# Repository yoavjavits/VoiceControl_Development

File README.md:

# Voice Control

This repo shows our development process.

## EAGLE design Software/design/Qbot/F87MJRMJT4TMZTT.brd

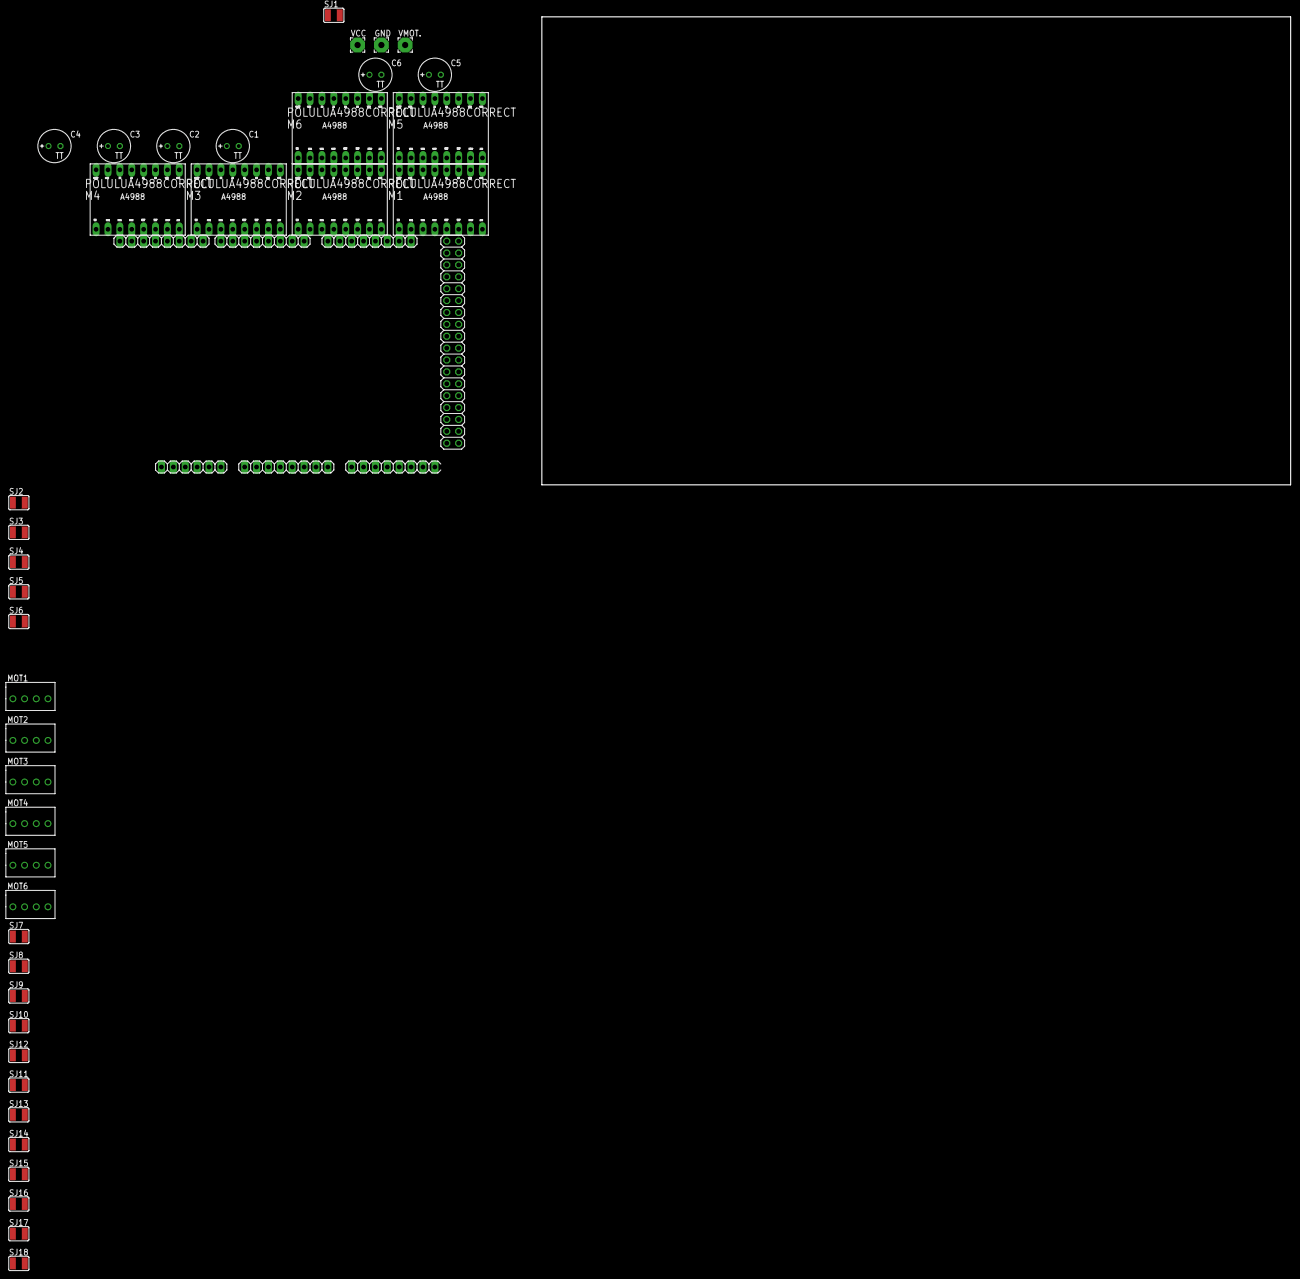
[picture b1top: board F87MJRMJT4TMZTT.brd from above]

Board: 2 copper layers, 160.0 x 100.0 mm, 40 parts (0 on the bottom side), 61 nets, no tracks yet.

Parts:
C1, C2, C3, C4, C5, C6: 100µF; TT2D7
GND: 3,17/1,3
IC2: MEGA_ARDUINO_1
M1, M2, M3, M4, M5, M6: POLULUA4988CORRECT; POLULU_A4988
MOT1, MOT2, MOT3, MOT4, MOT5, MOT6: 4PIN_JST
SJ1, SJ2, SJ3, SJ4, SJ5, SJ6, SJ7, SJ8, SJ9, SJ10, SJ11, SJ12, SJ13, SJ14, SJ15, SJ16, SJ17, SJ18: SJW
VCC: 3,17/1,3
VMOT.: 3,17/1,3

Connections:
+5V: IC2.3, IC2.47, IC2.48
GND: C1.-, C2.-, C3.-, C4.-, C5.-, C6.-, GND.1, IC2.4, IC2.5, IC2.45, IC2.81, IC2.82, M1.GND@1, M1.GND@2, M2.GND@1, M2.GND@2, M3.GND@1, M3.GND@2, M4.GND@1, M4.GND@2, M5.GND@1, M5.GND@2, M6.GND@1, M6.GND@2
MOT1DIR: IC2.33, M1.STEP
MOT1STEP: IC2.34, M1.DIR
MOT2DIR: IC2.35, M2.STEP
MOT2STEP: IC2.36, M2.DIR
MOT3DIR: IC2.37, M3.STEP
MOT3STEP: IC2.38, M3.DIR
MOT4DIR: IC2.39, M4.STEP
MOT4STEP: IC2.40, M4.DIR
MOT5DIR: IC2.41, M5.STEP
MOT5STEP: IC2.42, M5.DIR
MOT6DIR: IC2.43, M6.STEP
MOT6STEP: IC2.44, M6.DIR
unnamed: M1.MS1, SJ1.2
unnamed: M1.MS2, SJ2.2
unnamed: M1.MS3, SJ3.2
unnamed: M1.2B, MOT1.1
unnamed: M1.2A, MOT1.2
unnamed: M1.1A, MOT1.3
unnamed: M1.1B, MOT1.4
unnamed: M2.MS1, SJ4.2
unnamed: M2.MS2, SJ5.2
unnamed: M2.MS3, SJ6.2
unnamed: M2.2B, MOT2.1
unnamed: M2.2A, MOT2.2
unnamed: M2.1A, MOT2.3
unnamed: M2.1B, MOT2.4
unnamed: M2.!RESET, M2.!SLEEP
unnamed: M3.2B, MOT3.1
unnamed: M3.2A, MOT3.2
unnamed: M3.1A, MOT3.3
unnamed: M3.1B, MOT3.4
unnamed: M3.!RESET, M3.!SLEEP
unnamed: M4.2B, MOT4.1
unnamed: M4.2A, MOT4.2
unnamed: M4.1A, MOT4.3
unnamed: M4.1B, MOT4.4
unnamed: M4.!RESET, M4.!SLEEP
unnamed: M4.MS1, SJ10.2
unnamed: M4.MS2, SJ11.2
unnamed: M4.MS3, SJ12.2
unnamed: M5.2B, MOT5.1
unnamed: M5.2A, MOT5.2
unnamed: M5.1A, MOT5.3
unnamed: M5.1B, MOT5.4
unnamed: M5.!RESET, M5.!SLEEP
unnamed: M5.MS1, SJ13.2
unnamed: M5.MS2, SJ14.2
unnamed: M5.MS3, SJ15.2
unnamed: M6.2B, MOT6.1
unnamed: M6.2A, MOT6.2
unnamed: M6.1A, MOT6.3
unnamed: M6.1B, MOT6.4
unnamed: M6.!RESET, M6.!SLEEP
unnamed: M6.MS1, SJ16.2
unnamed: M6.MS2, SJ17.2
unnamed: M6.MS3, SJ18.2
unnamed: M1.!RESET, M1.!SLEEP
VCC: IC2.6, M1.VDD, M2.VDD, M3.VDD, M4.VDD, M5.VDD, M6.VDD, SJ1.1, SJ2.1, SJ3.1, SJ4.1, SJ5.1, SJ6.1, SJ7.1, SJ8.1, SJ9.1, SJ10.1, SJ11.1, SJ12.1, SJ13.1, SJ14.1, SJ15.1, SJ16.1, SJ17.1, SJ18.1, VCC.1
VMOT: C1.+, C2.+, C3.+, C4.+, C5.+, C6.+, M1.VMOT, M2.VMOT, M3.VMOT, M4.VMOT, M5.VMOT, M6.VMOT, VMOT..1

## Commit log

2022-03-30 Second Comment
2022-03-30 Second Commit
2022-03-30 Third Commit
2022-03-30 Hello
2022-04-05 Create voice recognition links
2022-04-05 I2S first try
2022-04-06 Create audio_serial_plotter
2022-04-06 Create recorder
2022-04-06 Create upload_to_browser
2022-04-06 Rename voice recognition links to voice_recognition_links.md
2022-04-12 Rename other_gits.md to Link To Other GitHub Projects
2022-04-12 Rename voice_recognition_links.md to Voice Recognition Links.md
2022-04-12 Rename Audio_Device.md to Audio Device.md
2022-04-12 Update Link To Other GitHub Projects
2022-04-12 WifiIntercom Upload
2022-04-12 Upload WifiIntercom
2022-04-13 Start Work Detector
2022-04-13 Rename Link To Other GitHub Projects to Link To Other GitHub Projects.md
2022-04-25 Create try
2022-04-26 TrainModel and OtherGits
2022-04-27 Upload ModelCC
2022-04-27 Run test on first go model
2022-04-29 Just minor change
2022-05-01 command detector
2022-05-01 Create Understand_RTOS
2022-05-01 updated wake word detector
2022-05-01 fixed
2022-05-01 Rename Understand_RTOS to Understand_RTOS.md
2022-05-02 WakeWord impovment
2022-05-02 last
2022-05-02 firmware push
2022-05-02 update few things
2022-05-02 copying alexa
2022-05-02 wake word update
2022-05-02 push
2022-05-02 before important changes
    move also the wait time to wake_word_detector
2022-05-03 nothing is working, i am going to try something else
2022-05-03 Lot of changes
2022-05-03 TwoModelOnESp works, kind of
2022-05-03 change folders
2022-05-03 commit gitignore
2022-05-03 fixed two models
2022-05-03 final network handle
2022-05-03 design
2022-05-05 upload go network
2022-05-05 upload 6 word (up down) network
2022-05-06 upload 6 word (one zero) network
2022-05-06 upload 3 words model
2022-05-06 upload 3 words model (forward, left, up)
2022-05-06 need to change the code - i only created folder
2022-05-06 need to keep working on it
2022-05-07 upload two model split network and other changes to previous models
2022-05-08 upload BRD network
2022-05-09 upload GOFLU
2022-05-09 change BDR model predication
2022-05-10 almost fixed
2022-05-10 another
2022-05-17 upload qbot SW
2022-05-19 update documentation
2022-05-23 push .vscode
2022-05-25 move 6 steppers
2022-05-25 changes in folders and connection
2022-05-29 start of robot code
2022-05-29 remote movement
2022-05-30 Rename FireBase Link.md to FireBaseLink.md
2022-05-30 add application
2022-05-30 add app
2022-05-30 send date to firebase
2022-05-30 add connection
2022-06-12 Rename Ideas.m to Ideas.md
2022-06-20 GOLEARN and FireBase
2022-07-06 wifi solved
2022-07-25 Rename Readme to Readme.md
